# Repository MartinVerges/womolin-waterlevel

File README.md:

# womolin.tanklevel

DIY project to build a smart tank level sensor for RVs or in other projects.
It is based on air pressure and is able to measure fresh water as well as grey and black water levels with high precision.

This project is still in development, it's a working sensor and I'm happy about pull requests to add more functionality, improve existing ones or just feedback.

## Why?

After I have long found on the market for camping nothing that is on the one hand affordable and on the other hand also technically good, I have started the development of my own tank sensor.

Thanks to the ESP32 this can be queried directly via WLAN or Bluetooth.
In addition MQTT, the sensor value can be pushed into an MQTT broker.

## Focus of this Project

The following aspects are the focus of this project:

 * Easy to use and rebuild
 * Precise in the evaluation of the data
 * Stand alone usable
 * Usable in all type of liquids

## Show me how it looks

#### Video Demonstration

#### Screenshots from the mobile UI

#### Photos of the prototype

#### Photos of the immersion tube

#### Schematics

#### Housing

The 3D printed housing can be found on [onshape as a editable document](https://cad.onshape.com/documents/dc5b401f0da730c8b1faabf2/w/d0c67204fcfba4efb6f8e658/e/1418b0722486737a7a11290c?renderMode=0&uiState=61bdca68d4b418569530fb02), or inside the folder [housing/*](housing/) as STL files.

## BOM - Bill of Materials

To build this sensor yourself, you need:

 * 1x [ESP32 ESP32-WROOM-32](https://womolin.de/produkt/wemos-d1-mini-esp32/)
 * 1x MPX53DP Pressure Sensor (~8.00€)
 * 1x [HX711 24-bit ADC](https://womolin.de/produkt/hx711-breakout-board/)
 * 1x Pushbutton (~0.15€)
 * 1x Tube with 20mm outher dimension (~1€) [HDPE 20mm](https://www.hornbach.de/shop/KWL-PE-HD-Rohr-20-mm-Laenge-2-m-Stange-12-5-bar/10193149/artikel.html)
 * 1x Tube with 4mm inner width (~1€) [PVC 4x1mm](https://www.hornbach.de/shop/Aquariumschlauch-Weich-PVC-Schlauch-4-x-1-mm-transparent-Meterware/5806466/artikel.html)
 * 1x Mini Air Pump (~2€) [3V 370](https://www.alibaba.com/product-detail/3-7V-6V-12VAquarium-for-fish_1600385811993.html)
 * 1x Small 12V to 5V power supply (~1€)
 * 1x PG screw fitting in the dimension for the 20mm tube
 * 1x Connector for the Tank itself, strongly depending on your individual situation
 
 In addition you need some few small cables and soldering equipment to build the circuit.

## Webinstaller

To make it super simple, our pre build firmware can be uploaded to your ESP32 using our Webinstaller.
You can find it at [https://webinstaller.womolin.de](https://webinstaller.womolin.de).

## OTA (Over-the-Air) Firmware files

If you want to update an already installed Sensor, you can upload the binarys directly to the sensor using the Web UI.
The latest version (current git main branch) is available at [https://s3.womolin.de/webinstaller/waterlevel-latest/firmware.bin](https://s3.womolin.de/webinstaller/waterlevel-latest/firmware.bin) and [https://s3.womolin.de/webinstaller/waterlevel-latest/littlefs.bin](https://s3.womolin.de/webinstaller/waterlevel-latest/littlefs.bin).

## How to build this PlatformIO based project

1. [Install PlatformIO Core](http://docs.platformio.org/page/core.html)
2. Run these commands:

```
    # Change directory into the code folder
    > cd womolin.tanklevel

    # Build project
    > platformio run -e esp32dev

    # Upload firmware
    > platformio run -e esp32dev --target upload
```

### Upload prebuild file

Here is a example command to upload existing firmware files.
```
/path/to/esptool.py --chip esp32 --port "/dev/ttyUSB0" --baud 921600 --before default_reset --after hard_reset \
    write_flash -z --flash_mode dio --flash_freq 80m --flash_size 4MB \
    0x1000 bootloader_dio_80m.bin \
    0x8000 partitions.bin \
    0xe000 boot_app0.bin \
    0x10000 firmware.bin \
    0x190000 firmware.bin \
    0x310000 littlefs.bin
```
Please make sure that your ESP32 runs with these settings before uploading it.

## How to build the UI

As the UI requires a valid FontAweSome License, you can find a generated `littlefs.bin` with my subscription.
It's automatically uploaded to our S3 at [https://s3.womolin.de/webinstaller/gaslevel-latest/littlefs.bin](https://s3.womolin.de/webinstaller/gaslevel-latest/littlefs.bin).
Please feel free to take this one for your sensor.

### Build your own littlefs.bin

As I haven't found good icons with a free license, I choosed the pro version of fontawesome.
Therefore it's required to have a valid subscription in order to build the UI yourself.

Set your FontAweSome key:
```
npm config set "@fortawesome:registry" https://npm.fontawesome.com/
npm config set "//npm.fontawesome.com/:_authToken" XXXXXXXXXXXXXXXXXXXX
```

Build the UI:
```
cd ui
npm install
npm run build
cd ..
pio run -e esp32dev -t buildfs
```

## Operation

When the sensor is started for the first time, a WiFi configuration portal opens via which a connection to the central access point can be established.
As soon as the connection has been established, the sensor is available on the IP assigned by the DHCP and the hostname [tanklevel.local](http://tanklevel.local) provided by MDNS.
You can now log in to the webobverface and proceed with the sensor setup. 
To obtain a tank level, it is necessary to measure the tank.
This can be done in 2 different ways:

1) Uniformly shaped tanks whose water level rises evenly.
2) Unevenly shaped tanks that contain bulges, tapers or other complex shapes.

### Uniform

Install the Sensor in an empty Tank, navigate to the [setup](http://tanklevel.local/setup/).
Press the button to determine the lower value of the tank. The value then appears in the input field. 

### Unevenly

Install the Sensor in an empty Tank, navigate to the [setup](http://tanklevel.local/setup/).
Prepare everything to achieve a constant inflow into the tank.
The best way to do this is to use water connections to city networks with a larger cross-section.
Refueling through this water connection should be done within about 3 minutes.

Once you have prepared everything, start the setup and now turn on the water tap.
The sensor now determines the increase in water level and calculates the percentage distribution in the tank at the end of the process.
Once the tank is completely filled, turn off the water supply and wait about 5 seconds before completing the setup via the web interface so that the pressure can normalize.

## Android Bluetooth Low Energy (BLE) App

This sensor can be displayed using my [Android App](https://github.com/MartinVerges/smartsensors/). 

## Power saving mode

This sensor is equipped with various techniques to save power.
Unfortunately, the operation of WiFi causes relatively high power consumption (__45~55mA idle__, up to 250mA during transmission).
This is not a problem in RVs with larger batteries or solar panels, but may be too high in small installations.
Therefore, the WiFi module can be easily and conveniently switched off via the web interface, putting the sensor into a deep sleep mode.
Here, the consumption of the esp32 officially drops to about 10μA.
Including the used step down power supply it will still consume __12.2mA in this sleep mode__ with RTC ADC enabled, so around 1/4 of full featured wifi enabled consumtion.
At regular intervals, the sensor switches on briefly, checks the tank level and updates the analog output of the sensor.

Since the WiFi portal is not available in this mode, you can reactivate the WiFi by pressing the button on the device once.

## Wifi connection failed or unable to interact

The button on the device switches from Powersave to Wifi Mode.
When the button is pressed again, the sensor restarts and opens its own access point.
Here you can correct the WLAN data.

## Alternatives

### Pressure based (like this project)

The only know alternative SuperSense tank sensor is available at around 259€ for purchase, but the price is extremely high and the data cannot be accessed digitally as it's proprietary.

### Resistance based

There are a lot of cheapest probes which all show only rough and mostly wrong data.
These are mostly based on measuring the resistance or continuity between two or more conductive rods that come into contact with water.

These probes usually cost more than the components in this project, but are extremely inaccurate, prone to calcification and malfunction.

## Using it with Home Assistant

To use the data of the sensor in the best possible way from the MQTT in HomeAssistant, here is an example configuration.
Please put it into your `configuration.yaml` file.

```
mqtt:
  sensor:
    - name: "Freshwater Level"
      unique_id: "freshwaterlevel"
      state_topic: "freshwater/tanklevel1"
      unit_of_measurement: "%"
      icon: "mdi:water-percent"

    - name: "Freshwater sensor temperature"
      unique_id: "freshwatertemp"
      state_topic: "freshwater/temperature1"
      unit_of_measurement: "°C"
      icon: "mdi:temperature-celsius"

    - name: "Freshwater sensor air pressure"
      unique_id: "freshwaterpressure"
      state_topic: "freshwater/airPressure1"
      unit_of_measurement: "hPa"
      icon: "mdi:gauge"

```
Your dashboard configuration could look like that:

```
square: false
columns: 2
type: grid
cards:
  - type: vertical-stack
    cards:
      - type: gauge
        entity: sensor.freshwater_level
        severity:
          green: 50
          yellow: 20
          red: 0
        needle: false
        min: 0
        max: 100
      - type: entities
        entities:
          - entity: sensor.freshwater_sensor_temperature
            name: Temp.
          - entity: sensor.freshwater_sensor_air_pressure
            name: Airpres.
        show_header_toggle: false
```

# License

womolin.tanklevel (c) by Martin Verges.

This Project is licensed under a Creative Commons Attribution-NonCommercial-ShareAlike 4.0 International License.

You should have received a copy of the license along with this work.
If not, see <http://creativecommons.org/licenses/by-nc-sa/4.0/>.

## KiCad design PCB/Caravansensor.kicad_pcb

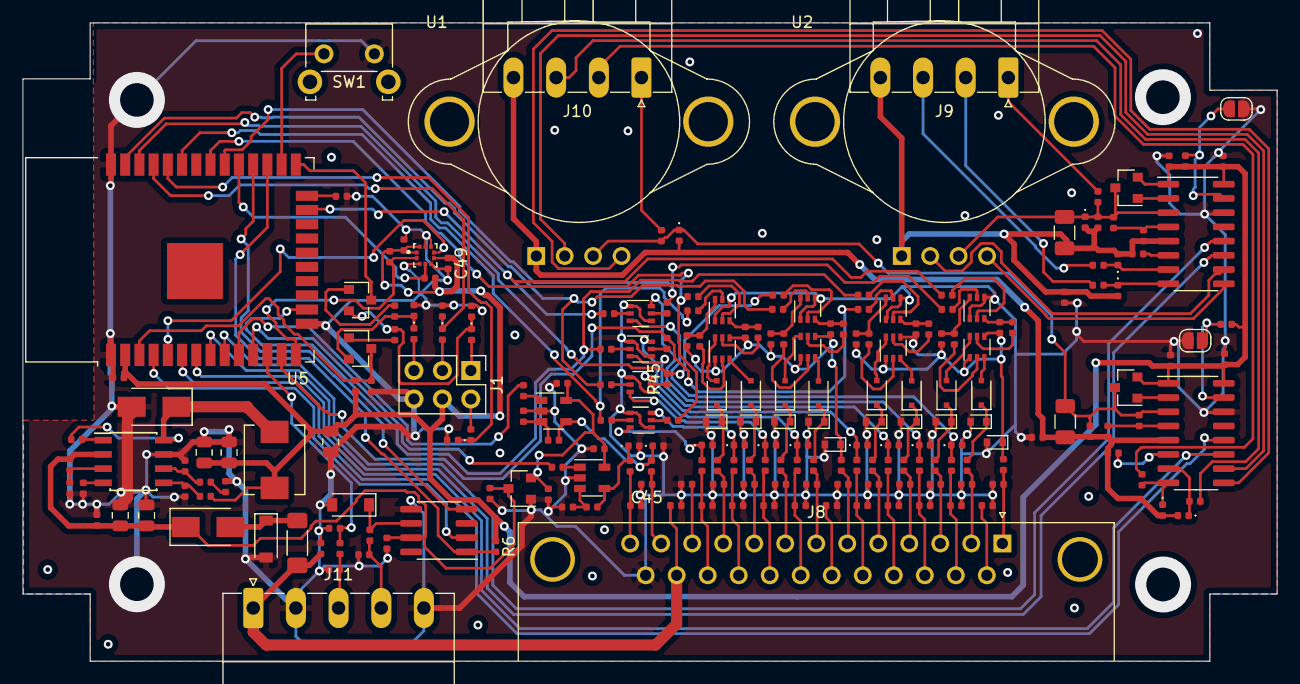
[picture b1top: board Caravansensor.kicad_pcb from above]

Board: 2 copper layers, 112.0 x 57.0 mm, 226 parts (0 on the bottom side), 164 nets.

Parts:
C1, C2, C5, C6, C7, C8, C9, C10, C11, C12, C13, C14, C20, C21, C40, C41, C42, C43, C44, C47, C48, C49, C53: 100n; C_0402_1005Metric
C3, C4: 10u; C_1206_3216Metric
C15, C52: 100p; C_0402_1005Metric
C16, C17: 4u7; C_0805_2012Metric
C18, C51: 1n; C_0402_1005Metric
C19: 47p; C_0402_1005Metric
C22, C23, C50: 47u; C_0805_2012Metric
C24, C25, C26, C27, C28, C29, C30, C31, C32, C33, C34, C35, C36, C37, C38, C39, C45, C46: 10n; C_0402_1005Metric
D1, D3: SMF16A; D_SOD-123
D2, D4: B340A; D_SMA
D5, D6, D7, D8, D17, D18, D19, D20, D31, D32, D33, D34, D35, D36, D37, D38, D39, D40, D41, D42, D43: RCLAMP0521P-N; D_0402_1005Metric
D9, D10, D11, D12, D21, D22, D23, D24: 1N4148WS; D_SOD-323F
D13, D14, D15, D16, D25, D26, D27, D28, D29, D30: ESD5Z15V; D_SOD-523
F1: Polyfuse; Fuse_1806_4516Metric
J1: Conn_02x03_Odd_Even; PinHeader_2x03_P2.54mm_Vertical
J8: DB25_Female; DSUB-25_Female_Horizontal_P2.77x2.84mm_EdgePinOffset7.70mm_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
J9, J10: Conn_01x04; PhoenixContact_MC_1,5_4-G-3.81_1x04_P3.81mm_Horizontal
J11: Conn_01x05; PhoenixContact_MC_1,5_5-G-3.81_1x05_P3.81mm_Horizontal
JP2, JP3: Jumper_2_Open; SolderJumper-2_P1.3mm_Open_RoundedPad1.0x1.5mm
L1: SLO0630H6R8MTT; L_Neosid_SM-PIC0512H
L2, L3: L; L_0402_1005Metric
Q1, Q2: MMBTA92-Transistor_BJT; SOT-23
Q3, Q4: MMBT5401; SOT-23
Q5, Q6, Q7, Q8, Q11, Q12, Q13, Q14: LBSS260DW; SOT-363_SC-70-6
Q9, Q10, Q15, Q16: LBSS84DW; SOT-363_SC-70-6
R1, R3: 20k; R_0402_1005Metric
R2, R4: 8k2; R_0402_1005Metric
R5, R6, R8, R9, R19, R20, R21, R22, R23, R24, R25, R26, R27, R28, R29, R30, R31, R32, R33, R34, R43, R44, R45, R46, R47, R48, R49, R50, R51, R52, R53, R54, R55, R56, R57, R58, R90, R91: 10k; R_0402_1005Metric
R7, R13, R14, R15, R16, R71, R72, R77, R78, R79, R80, R81, R82, R83, R84, R85, R89: 100r; R_0402_1005Metric
R10: 332k; R_0402_1005Metric
R11: 68k1; R_0402_1005Metric
R12: 29k4; R_0402_1005Metric
R17: 10k2; R_0402_1005Metric
R18: 3k24; R_0402_1005Metric
R35, R36, R37, R38, R39, R40, R41, R42, R59, R60, R61, R62, R63, R64, R65, R66, R67, R69, R75, R76: 1k; R_0402_1005Metric
R68, R70: 200k; R_0402_1005Metric
R73, R74: 100k; R_0402_1005Metric
R86, R87: 4k7; R_0402_1005Metric
R88: 12k; R_0402_1005Metric
SW1: TS-1093A-A12B3-D2; SW_Tactile_SKHH_Angled
U1, U2: MPX53; 344C
U3, U4: HX711; SOIC-16_3.9x9.9mm_P1.27mm
U5: ESP32-WROOM-32D; ESP32-WROOM-32
U6: TJA1021T; SOIC-8_3.9x4.9mm_P1.27mm
U7: TPS54331D; SOIC-8_3.9x4.9mm_P1.27mm
U8, U9: LMV321; SOT-23-5
U10: BMP388; PQFN50P200X200X80-10N
U11: ME6209A50M3G; SOT-23

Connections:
1_Wire: D39.1, R89.2, U5.12
+3V3: C7.1, C8.1, C9.1, C10.1, C12.1, C22.1, C23.1, C49.1, C50.1, C53.1, J1.4, L1.2, Q1.2, Q2.2, R6.1, R17.1, R86.1, R87.1, R88.1, R90.2, R91.2, U3.1, U3.16, U4.1, U4.16, U5.2, U10.1, U10.6, U10.10
+5V: C40.2, C41.2, C48.1, U8.5, U9.5, U11.2
+BATT: C13.1, C14.1, C16.1, C17.1, C47.1, D2.1, R10.1, U6.7, U7.2, U11.3
BME_INT: U5.5, U10.7
FW_25: R22.2, R26.2, U5.30
FW_25_out_neg: C27.1, J8.15, R38.2
FW_25_out_pos: C31.1, J8.2, R42.2
FW_50: R21.2, R25.2, U5.23
FW_50_out_neg: C26.1, J8.16, R37.2
FW_50_out_pos: C30.1, J8.3, R41.2
FW_75: R20.2, R24.2, U5.13
FW_75_out_neg: C25.1, J8.17, R36.2
FW_75_out_pos: C29.1, J8.4, R40.2
FW_100: R19.2, R23.2, U5.16
FW_100_out_neg: C24.1, J8.18, R35.2
FW_100_out_pos: C28.1, J8.5, R39.2
FW_Analog_ESP: R67.2, U5.10
FW_Analog_out: C45.1, J8.12, R75.1
GND: C7.2, C8.2, C9.2, C10.2, C11.2, C12.2, C13.2, C14.2, C15.2, C16.2, C17.2, C19.2, C20.2, C22.2, C23.2, C24.2, C25.2, C26.2, C27.2, C28.2, C29.2, C30.2, C31.2, C32.2, C33.2, C34.2, C35.2, C36.2, C37.2, C38.2, C39.2, C40.1, C41.1, C42.2, C43.2, C44.2, C45.2, C46.2, C47.2, C48.2, C49.2, C50.2, C51.2, C52.2, C53.2, D1.2, D3.2, D4.2, D5.2, D6.2, D7.2, D8.2, D13.2, D14.2, D15.2, D16.2, D17.2, D18.2, D19.2, D20.2, D25.2, D26.2, D27.2, D28.2, D29.2, D30.2, D31.2, D32.2, D39.2, D40.2, D41.2, D42.2, D43.2, J1.6, J8.25, J11.2, J11.5, JP2.2, JP3.2, L2.2, L3.2, Q5.1, Q5.4, Q6.1, Q6.4, Q7.1, Q7.4, Q8.1, Q8.4, Q11.1, Q11.4, Q12.1, Q12.4, Q13.1, Q13.4, Q14.1, Q14.4, R5.2, R11.2, R12.2, R18.2, R68.2, R70.2, R77.2, R78.2, R79.2, SW1.2, U3.14, U4.14, U5.1, U5.15, U5.38, U6.5, U7.7, U8.2, U9.2, U10.3, U10.5, U10.8, U10.9, U11.1
GPIO_0: Q3.3, U5.25
INA_N_1: D38.1, R85.1, U4.7
INA_N_2: D37.1, R82.1, U3.7
INA_P_1: D36.1, R84.1, U4.8
INA_P_2: D35.1, R81.1, U3.8
LIN: C15.1, J11.4, R7.1
LIN_RX: R6.2, U5.27, U6.1
LIN_SLP: U5.4, U6.2
LIN_TX: U5.28, U6.4
unnamed: C1.1, C3.1, D33.1, Q1.3, R1.1, R80.1, U1.3, U3.3
unnamed: C1.2, C3.2, C5.2, D33.2, D35.2, D37.2, J10.4, L2.1, R2.2, U1.1, U3.5
unnamed: C2.1, C4.1, D34.1, Q2.3, R3.1, R83.1, U2.3, U4.3
unnamed: C2.2, C4.2, C6.2, D34.2, D36.2, D38.2, J9.4, L3.1, R4.2, U2.1, U4.5
unnamed: C5.1, U3.6
unnamed: C6.1, U4.6
unnamed: C18.1, C19.1, U7.6
unnamed: C18.2, R12.1
unnamed: C20.1, U7.4
unnamed: C21.1, U7.1
unnamed: C21.2, D4.1, L1.1, U7.8
unnamed: C42.1, J8.1, R71.2
unnamed: C43.1, J8.6, R72.2
unnamed: C52.1, J11.3, R89.1
unnamed: D1.1, D2.2, F1.1
unnamed: D3.1, R7.2, U6.6
unnamed: D5.1, Q7.6, R35.1
unnamed: D6.1, Q7.3, R36.1
unnamed: D7.1, Q8.6, R37.1
unnamed: D8.1, Q8.3, R38.1
unnamed: D9.2, Q9.6
unnamed: D10.1, D14.1, R40.1
unnamed: D10.2, Q9.3
unnamed: D11.1, D15.1, R41.1
unnamed: D11.2, Q10.6
unnamed: D12.1, D16.1, R42.1
unnamed: D12.2, Q10.3
unnamed: D9.1, D13.1, R39.1
unnamed: D17.1, Q11.6, R59.1
unnamed: D18.1, Q11.3, R60.1
unnamed: D19.1, Q12.6, R61.1
unnamed: D20.1, Q12.3, R62.1
unnamed: D21.1, D25.1, R63.1
unnamed: D21.2, Q15.6
unnamed: D22.1, D26.1, R64.1
unnamed: D22.2, Q15.3
unnamed: D23.1, D27.1, R65.1
unnamed: D23.2, Q16.6
unnamed: D24.1, D28.1, R66.1
unnamed: D24.2, Q16.3
unnamed: D31.1, R73.1, R75.2, U8.4
unnamed: D32.1, R74.1, R76.2, U9.4
unnamed: J1.1, R13.1
unnamed: J1.2, R16.2
unnamed: J1.3, R14.1
unnamed: J1.5, R15.1
unnamed: J8.11, R79.1
unnamed: J8.14, R77.1
unnamed: J8.19, R78.1
unnamed: J9.1, R83.2
unnamed: J9.2, R84.2
unnamed: J9.3, R85.2
unnamed: J10.1, R80.2
unnamed: J10.2, R81.2
unnamed: J10.3, R82.2
unnamed: JP2.1, R90.1, U3.15
unnamed: JP3.1, R91.1, U4.15
unnamed: Q1.1, U3.2
unnamed: Q2.1, U4.2
unnamed: Q3.1, R8.2
unnamed: Q4.1, R9.1
unnamed: Q5.2, R19.1
unnamed: Q5.3, R28.2, R32.2
unnamed: Q5.5, R20.1
unnamed: Q5.6, R27.2, R31.2
unnamed: Q6.2, R21.1
unnamed: Q6.3, R30.2, R34.2
unnamed: Q6.5, R22.1
unnamed: Q6.6, R29.2, R33.2
unnamed: Q7.2, R23.1
unnamed: Q7.5, R24.1
unnamed: Q8.2, R25.1
unnamed: Q8.5, R26.1
unnamed: Q9.2, R31.1
unnamed: Q9.5, R32.1
unnamed: Q10.2, R33.1
unnamed: Q10.5, R34.1
unnamed: Q11.2, R43.1
unnamed: Q11.5, R44.1
unnamed: Q12.2, R45.1
unnamed: Q12.5, R46.1
unnamed: Q13.2, R47.1
unnamed: Q13.3, R52.2, R56.2
unnamed: Q13.5, R48.1
unnamed: Q13.6, R51.2, R55.2
unnamed: Q14.2, R49.1
unnamed: Q14.3, R54.2, R58.2
unnamed: Q14.5, R50.1
unnamed: Q14.6, R53.2, R57.2
unnamed: Q15.2, R55.1
unnamed: Q15.5, R56.1
unnamed: Q16.2, R57.1
unnamed: Q16.5, R58.1
unnamed: R1.2, R2.1, U3.4
unnamed: R3.2, R4.1, U4.4
unnamed: R5.1, U5.24
unnamed: R10.2, R11.1, U7.3
unnamed: R17.2, R18.1, U7.5
unnamed: R67.1, U8.1
unnamed: R68.1, R73.2, U8.3
unnamed: R69.1, U9.1
unnamed: R70.1, R74.2, U9.3
unnamed: U1.2, U3.10
unnamed: U1.4, U3.9
unnamed: U2.2, U4.10
unnamed: U2.4, U4.9
unnamed: U3.11, U5.7
unnamed: U3.12, U5.6
unnamed: U4.11, U5.8
unnamed: U4.12, U5.9
PGM_CTS: D42.1, Q4.2, R8.1, R15.2
PGM_DTR: D40.1, Q3.2, R9.2, R13.2
PGM_RX: D43.1, R16.1, U5.34
PGM_TX: D41.1, R14.2, U5.35
Reset: C51.1, Q4.3, R88.2, U5.3
SCL: R86.2, U5.14, U10.2
SDA: R87.2, U5.29, U10.4
VBUS: C11.1, C44.1, F1.2, J8.24, J11.1
VCC: D29.1, Q9.1, Q9.4, Q10.1, Q10.4, R27.1, R28.1, R29.1, R30.1, R71.1
VCCQ: D30.1, Q15.1, Q15.4, Q16.1, Q16.4, R51.1, R52.1, R53.1, R54.1, R72.1
WLAN: SW1.1, U5.26
WW_25: R46.2, R50.2, U5.37
WW_25_out_neg: C35.1, J8.20, R62.2
WW_25_out_pos: C39.1, J8.7, R66.2
WW_50: R45.2, R49.2, U5.36
WW_50_out_neg: C34.1, J8.21, R61.2
WW_50_out_pos: C38.1, J8.8, R65.2
WW_75: R44.2, R48.2, U5.33
WW_75_out_neg: C33.1, J8.22, R60.2
WW_75_out_pos: C37.1, J8.9, R64.2
WW_100: R43.2, R47.2, U5.31
WW_100_out_neg: C32.1, J8.23, R59.2
WW_100_out_pos: C36.1, J8.10, R63.2
WW_Analog_ESP: R69.2, U5.11
WW_Analog_out: C46.1, J8.13, R76.1

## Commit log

2021-12-12 working prototype
2021-12-12 rename main app file
2021-12-12 corrected README markdown format
2021-12-12 different EEPROM approach, still not working ;/
2021-12-12 lint fix
2021-12-12 remove EEPROM, add preferences
2021-12-12 Migrate to platformio, add webserver and OTA upd.
2021-12-13 Settings now stored and reloaded Added webserver for future use
2021-12-14 fix dependencies, initial linter config
2021-12-14 more small cleanup and fixes
2021-12-14 cleanup
2021-12-14 sensor function seperated
2021-12-14 new html5 frontend
2021-12-14 online status with live update
2021-12-14 fully working UI setup and Status
2021-12-15 massive api upgrade
    add lot's of entpoints for plain and json
    add alternative setup for linear tanks
    fixed dozens of bugs (to many to count)
    improved UI overall
    Current state of work, it's usable!
2021-12-16 add more images
2021-12-16 Add schematic
2021-12-18 Update README.md
    add video to show the function
2021-12-18 add housing pics to readme
2021-12-18 add 3D housing
2021-12-18 split up setup for different tanks
2021-12-19 added analog output (0-3.3V) and lots of improvem.
2021-12-21 restructure and split parts
2021-12-21 remove double reset detection
2021-12-23 increase precision, split code, more api, bugfixes
2021-12-23 migrated hx711 and preferences into class
2021-12-23 rename NVS variable
2021-12-23 reload settings on call of begin()
2021-12-23 add configuration dialog for hostname and wifi
2021-12-23 modal fix, push button enables wifi, then portal
2021-12-24 better documentation, DAC output, minor bugfixes
2021-12-24 fix build dependency issue
2021-12-24 fix build dependencies
2021-12-24 fix linter github action
2021-12-24 update github actions
2021-12-24 updated mklittlefs for windows, linux, and darwin
2021-12-24 fix lint for python
2021-12-24 python lint fix
2021-12-24 yet another lint fix
2021-12-24 drop linter
2021-12-24 update README, drop linter badge
2021-12-24 update readme and screenshots
2021-12-25 change ADC range from 0.5V=0% up to 3.0V=100%
2021-12-25 let wifi autoreconnect
2021-12-25 add http options for CORS to onNotFound
2021-12-30 Update README.md
    Add more power consumption details
2022-01-02 initial bluetooth support but now to large for OTA
2022-01-17 Add License, drop Bootstrap, add BLE
    Added a CC-NC-SA License to the project
    Dropped Bootstrap CSS and JS due to size
    Add working BLE stack to support the Android APP
    Migrated Configuration in a individual page
    Updated README and Screenshots
2022-01-18 add MQTT, more options and cleanup project
2022-01-19 greatly improved MQTT support and config options
2022-01-19 New screenshots, new API endpoints, fixed API bugs
    - Screenshots of the new configuration options
    - Reworked some API endpoints, fixed bugs like /api/level output
    - Fixed small HTML bugs
    - Updated API Insomnia config file
    - and more
2022-01-20 release v1.1
    - Configurable analog output
    - Connection to a MQTT broker and publish of the filling level
    - Compatible to Android APP to access via Bluetooth low energy (BLE)
    - Revised web frontend
    - under CC-NC-SA-v4 open source license
    - Advanced energy saving options
2022-02-22 BLE update, dependency upgrade
2022-03-03 improved irregular tank setup routine
2022-03-26 initial draft for RTC history storage
2022-03-31 rewrote MQTT connector
2022-04-09 First Schematic draft, include Interface for common caravan Panels (Arsilicii, CBE, Nordeletronica, Schaudt), LIN and onwire Interface for other controls.
2022-04-17 WifiManager: add config fallbackToSoftAp()
2022-04-17 update simple css v2
2022-04-17 WifiManager: remove entry function and API
2022-04-17 WifiManager: initial working version
2022-04-17 WIP: rewrite WiFi manager
2022-04-17 WifiManager: add Web UI to manage Wifi
2022-04-17 Wifi AP Hotspot name changed, timeout on 600sec
2022-04-17 minor improvents, faster wifi connect if only 1 ssid configured, better serial output
2022-04-17 some more optimizations
2022-04-17 moved wifi manger into external dependency
2022-04-17 minor fixes
2022-04-18 initial version to support multiple sensors on a single esp32
2022-04-22 configuration and mqtt updates
2022-04-24 Layout complete, LIN, Added, 1wire added, Power supply added
2022-04-28 updated hx711 library
2022-04-28 fix nvs storage bug, add airPump to repressurize, updated wifimanger, more
2022-04-29 drop air pump because it's not tight
2022-05-05 add initial functions to compensate using bmp pressure sensuor
2022-05-08 Upg to IDF 4.2 based arduino espressif32 framework
2022-05-20 use latest esp32-wifi-manager
2022-05-23 Revert "drop air pump because it's not tight"
    This reverts commit 07c289f8a3a6892c7248a57934f4b1f7d9e76e7b.
2022-05-23 working pump+bmp prototype
2022-05-23 UI update, allow tube repressurise
2022-06-03 add repressurize to UI, fixed MQTT user/pass bug
2022-06-12 add new UI files (not yet in use)
2022-06-12 add UI readme
2022-06-13 UI update
2022-06-13 build new gui into firmware
2022-06-14 drop old UI
2022-06-14 fixed issue with littlefs
2022-06-16 update GH action
2022-06-16 build mklittlefs with len 128 on the fly
2022-06-17 remove mklittlefs binary and add to gitignore
2022-06-17 GH action update
2022-07-10 huge change, still WIP, new UI and stuff
2022-07-12 add UI for unevenly formed tanks
2022-07-12 drop prebuild bin, should be done by GH action
2022-07-12 fix GH action
2022-07-14 fix web status
2022-07-15 update docs, pics, schematics. Drop insomnia spec
2022-07-17 use events for UI, migrated to another bmp180 lib
2022-07-17 correct schematic
2022-07-17 updated screenshots, pictures, docs
2022-07-17 add OTA update
2022-07-17 add /api/esp with lot's of details
2022-07-18 Add OTA functionality
2022-07-21 fix crash on missing bmp180, set ota mdns hostname
2022-07-21 refresh known ap list on add and delete
2022-07-21 reduce picture size
2022-07-26 GH release scripts
2022-08-21 migrated webserial, faster level display, ota improvements, ui update,... from gaslevel
2022-08-24 fix activity icon for multi pump sensors
2022-08-24 automatic repressurize on pressure change
2022-08-25 improved mqtt client connect message
2022-08-25 fix UI bug
2022-08-25 fix timing interval
2022-08-25 add ota partition details
2022-08-25 add api to allow partition switch
2022-08-25 fix api error
2022-08-25 fix airpump api function
2022-08-25 slower refresh update time
2022-08-26 provide volumetric information
2022-08-28 make auto pressurize reconfigurable
2022-08-30 cleanup and optimizations
2022-09-08 add doc for webupdater
2022-09-08 add BOM article links
2022-10-21 fix author email address
2022-11-08 cleanup and restructureing some code
2022-12-03 on otapassword change, directly set the new pass
2022-12-18 working sveltekit 1.0 - but to huge
2022-12-18 using scss again, still to large
2022-12-18 run UI as SPA application
2022-12-22 Add HomeAssistant config documentation
2022-12-22 fix release pipeline asset content type
2023-01-04 add api ui testing endpoint
2023-01-06 add versioning
2023-01-06 add current-version.json to output
2023-01-06 Update .gitlab-ci.yml file
2023-01-07 Versioning and Gitlab CI pipeline
2023-01-09 removed ArduinoOTA, added WebUpdate from S3,
2023-01-09 updated pipeline
2023-01-09 update pipeline
2023-02-26 fix IP address output from MQTT
2023-02-26 update CI/CD
2023-02-26 add missing manifest generator script
2023-03-19 update BOM
2023-05-04 fix #6: Add option to enable/disable air pump on boot
2023-08-23 Small fix for browser side verification in settings page
